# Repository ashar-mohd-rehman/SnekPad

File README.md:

I introduce you all to the SnekPad. Snekpad is a 6key macropad with an OLED display and a Volume knob. The oled display shows the stas, Volume and the SnekPad Logo. 
The volume knob is used for well, To contol volume and mute on a press. The Top keys are mapped to Copy,Paste,Cut and the bottom keys are mappable in ur desired software.
# Assembly

# PCB 

# Schematic

# Code Snippet

 # **BOM** #
| Item | Quantity | Price (USD) |
|-----|----------|-------------|
| Cherry MX Low Profile Switches | 10x | 2.70 |
| Blank DSA Keycaps | 10x | 2.20 |
| Chanzon 1N4148 Diodes | 100x | 2.73 |
| 0.91 inch OLED Display Module | 1x | 1.71 |
| Xiao RP2040 | 1x | 6.75 |
| EC11B5AI Rotary Encoder | 2x | 1.22 |
| Soldering Iron | 1x | 3.27 |
| PCB | 1x | 9.82 |
| **Total (Approx.)** |  | **31 – 35 USD** |

Link TO Bom : https://docs.google.com/spreadsheets/d/1mGxVifGTovYlbTKS4N1jqtnvdSKJnGPxNXVJJV7mGf4/edit?usp=sharing

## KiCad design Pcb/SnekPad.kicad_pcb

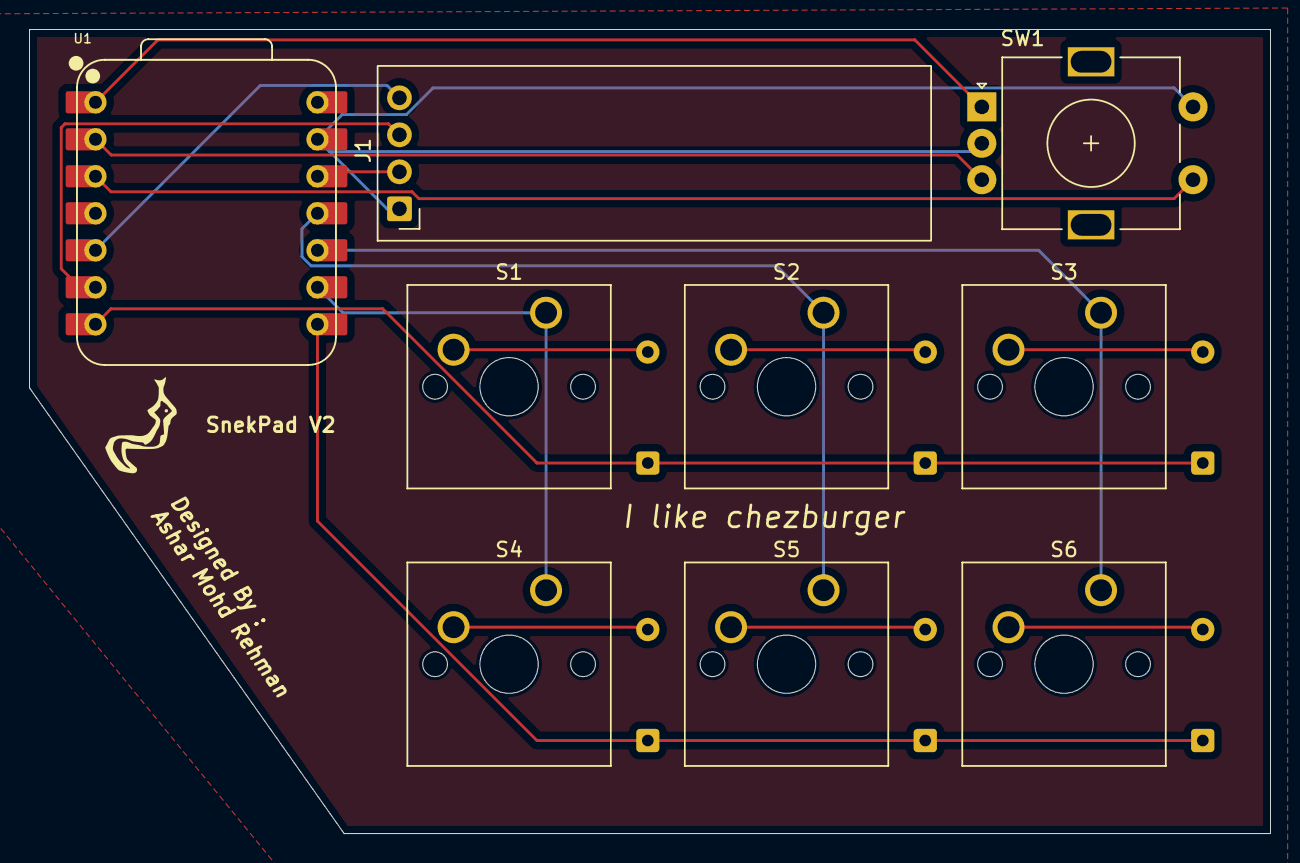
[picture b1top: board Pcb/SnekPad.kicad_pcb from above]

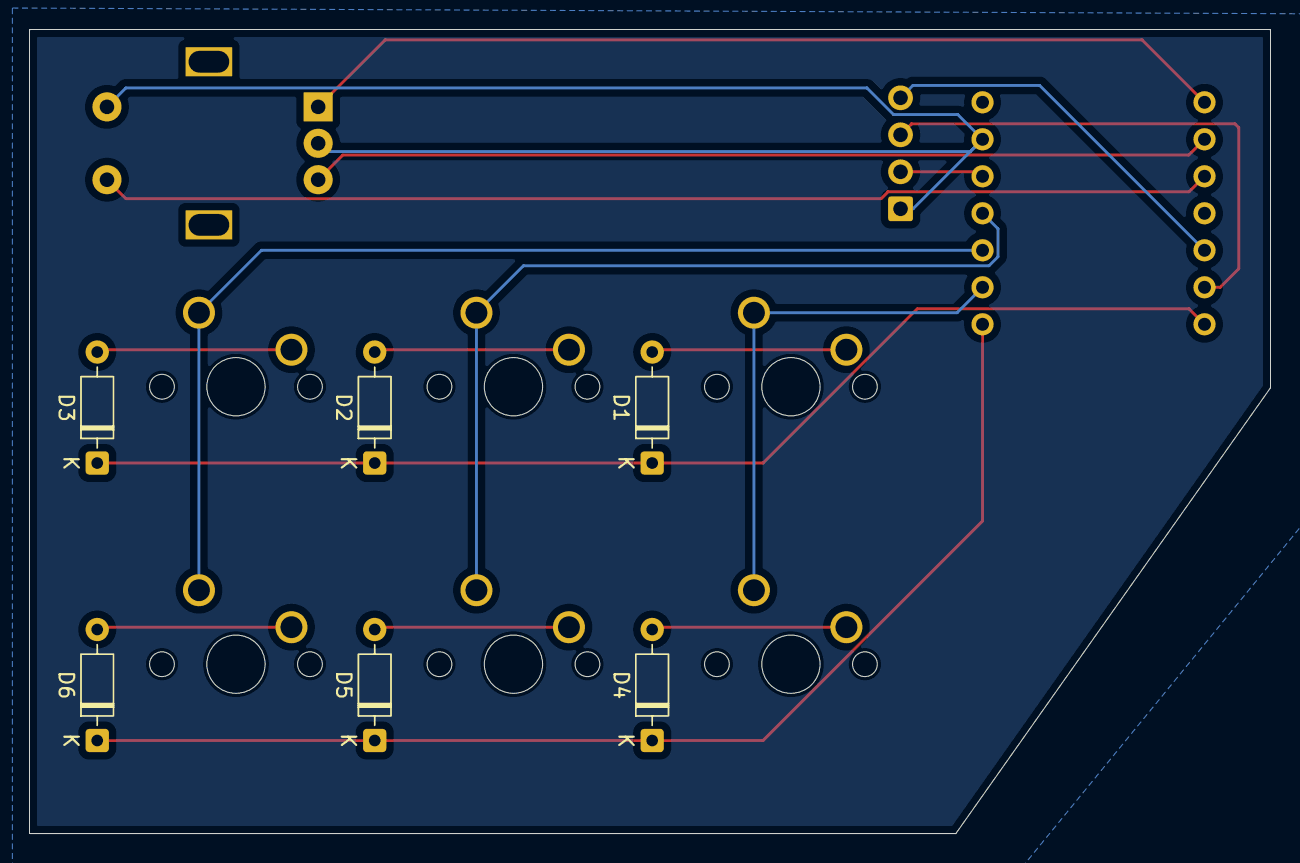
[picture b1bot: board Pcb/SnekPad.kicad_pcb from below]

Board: 2 copper layers, 85.2 x 55.2 mm, 15 parts (6 on the bottom side), 18 nets.

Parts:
D1, D2, D3, D4, D5, D6: D_DO-35_SOD27_P7.62mm_Horizontal
J1: OLED_128x32; OLED_0.91_128x32
S1, S2, S3, S4, S5, S6: SW_Cherry_MX_1.00u_PCB
SW1: RotaryEncoder_Switch; RotaryEncoder_Alps_EC11E-Switch_Vertical_H20mm
U1: XIAO-RP2040-DIP

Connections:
/Col 1: S1.1, S4.1, U1.9 (GPIO2/SCK)
/Col 2: S2.1, S5.1, U1.11 (GPIO3/MOSI)
/Col 3: S3.1, S6.1, U1.10 (GPIO4/MISO)
/Enc A: SW1.A, U1.1 (GPIO26/ADC0/A0)
/Enc B: SW1.B, U1.2 (GPIO27/ADC1/A1)
/Enc SW1: SW1.S1, U1.3 (GPIO28/ADC2/A2)
/Row 1: D1.1 (K), D2.1 (K), D3.1 (K), U1.7 (GPIO0/TX)
/Row 2: D4.1 (K), D5.1 (K), D6.1 (K), U1.8 (GPIO1/RX)
/SCL: J1.3 (SCL), U1.6 (GPIO7/SCL)
/SDA: J1.4 (SDA), U1.5 (GPIO6/SDA)
/VCC: J1.2 (VCC), U1.12 (3V3)
GND: J1.1 (GND), SW1.C, SW1.S2, U1.13 (GND)
unnamed: D1.2 (A), S1.2
unnamed: D2.2 (A), S2.2
unnamed: D3.2 (A), S3.2
unnamed: D4.2 (A), S4.2
unnamed: D5.2 (A), S5.2
unnamed: D6.2 (A), S6.2

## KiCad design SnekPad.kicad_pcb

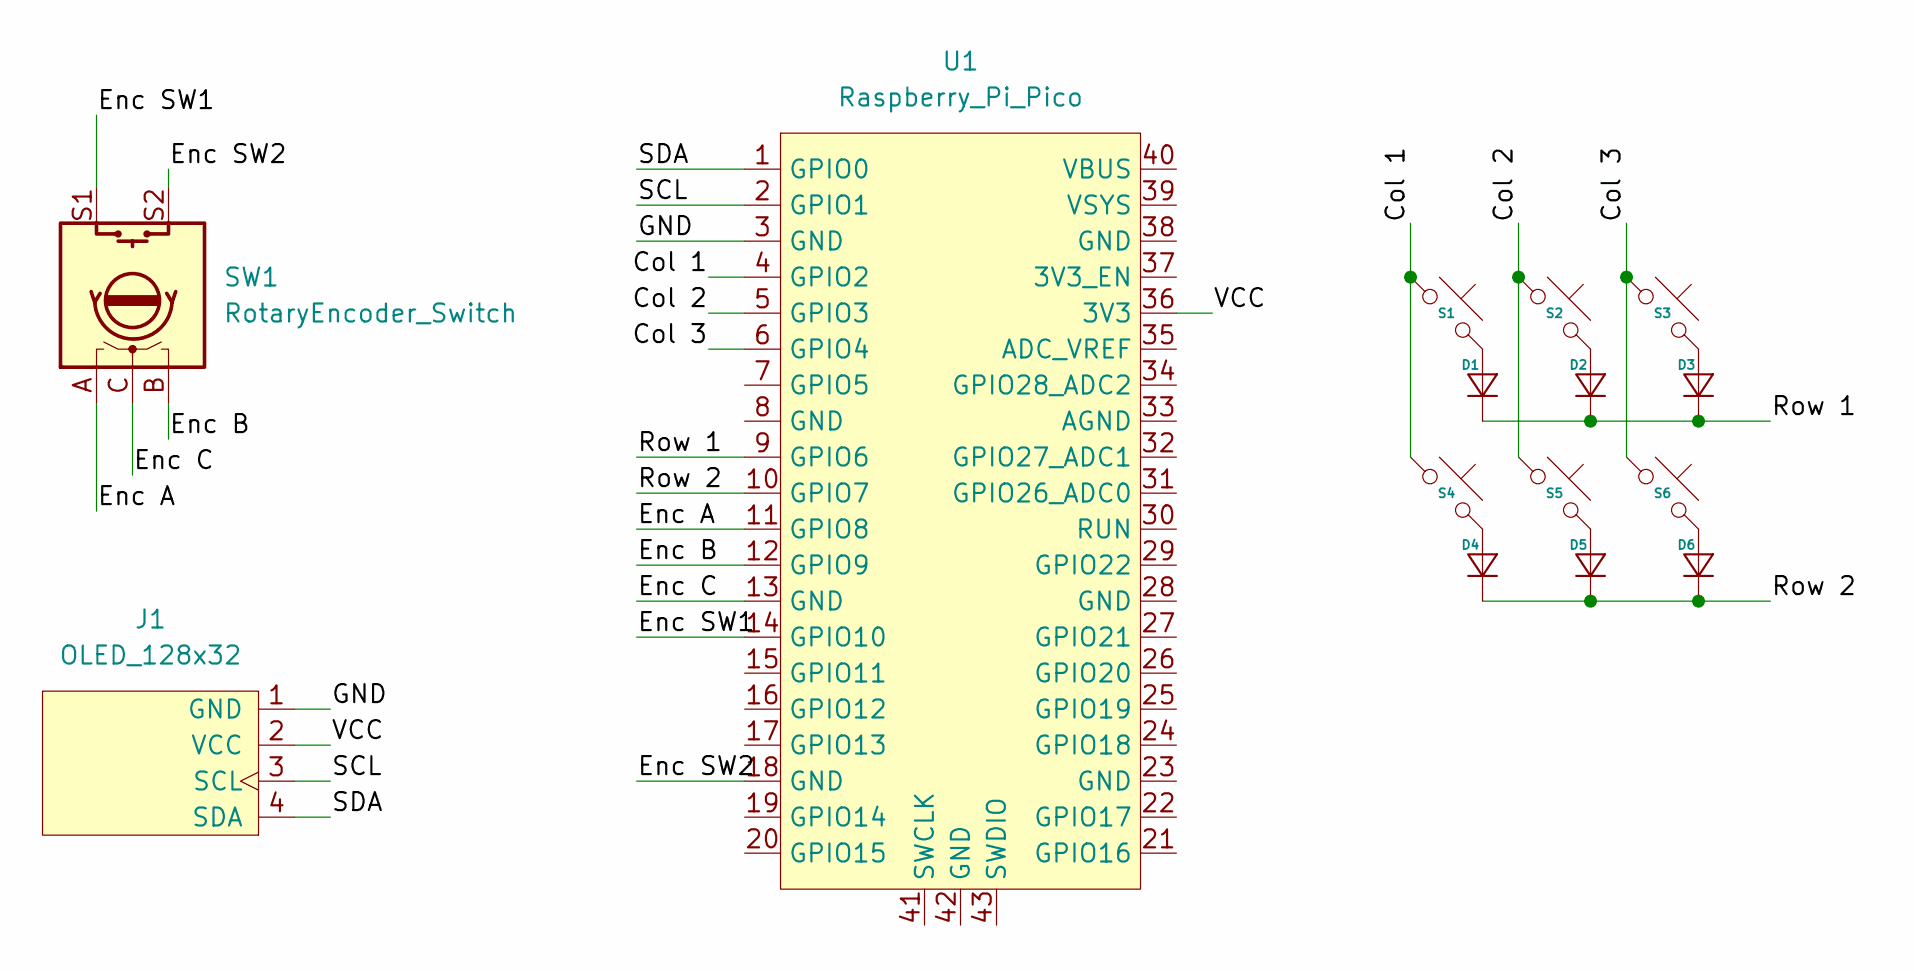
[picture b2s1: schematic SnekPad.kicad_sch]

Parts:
D1, D2, D3, D4, D5, D6: D_DO-35_SOD27_P7.62mm_Horizontal
J1: OLED_128x32
S1, S2, S3, S4, S5, S6: SW_Cherry_MX_1.00u_PCB
SW1: RotaryEncoder_Switch; RotaryEncoder_Alps_EC11E-Switch_Vertical_H20mm
U1: Raspberry_Pi_Pico; RaspberryPi_Pico_Common_THT

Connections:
/Col 1: S1.1, S4.1, U1.4 (GPIO2)
/Col 2: S2.1, S5.1, U1.5 (GPIO3)
/Col 3: S3.1, S6.1, U1.6 (GPIO4)
/Enc A: SW1.A, U1.11 (GPIO8)
/Enc B: SW1.B, U1.12 (GPIO9)
/Enc C: SW1.C, U1.13 (GND)
/Enc SW1: SW1.S1, U1.14 (GPIO10)
/Enc SW2: SW1.S2, U1.18 (GND)
/GND: J1.1 (GND), U1.3 (GND)
/Row 1: D1.1 (K), D2.1 (K), D3.1 (K), U1.9 (GPIO6)
/Row 2: D4.1 (K), D5.1 (K), D6.1 (K), U1.10 (GPIO7)
/SCL: J1.3 (SCL), U1.2 (GPIO1)
/SDA: J1.4 (SDA), U1.1 (GPIO0)
/VCC: J1.2 (VCC), U1.36 (3V3)
unnamed: D1.2 (A), S1.2
unnamed: D2.2 (A), S2.2
unnamed: D3.2 (A), S3.2
unnamed: D4.2 (A), S4.2
unnamed: D5.2 (A), S5.2
unnamed: D6.2 (A), S6.2

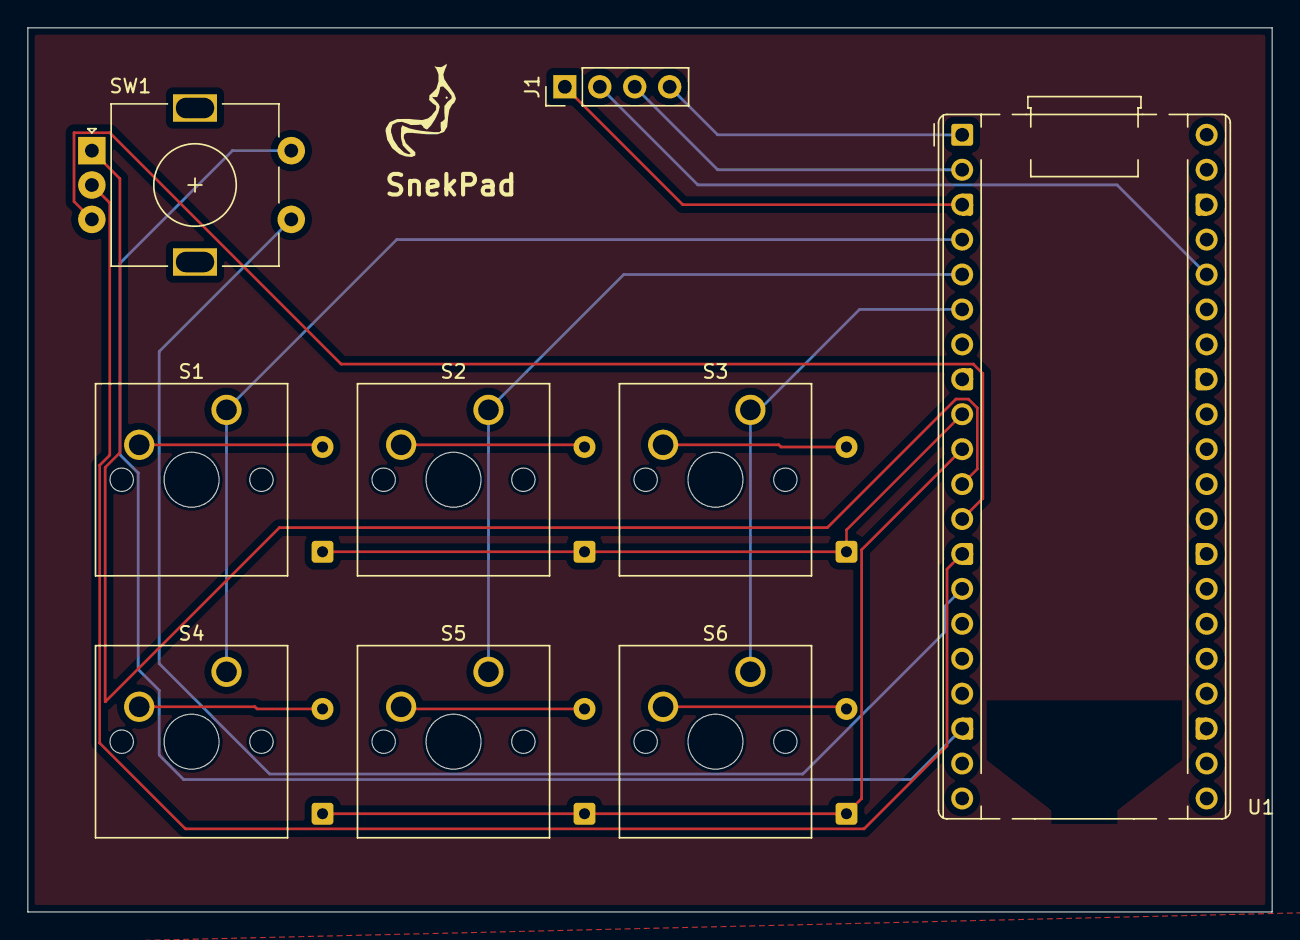
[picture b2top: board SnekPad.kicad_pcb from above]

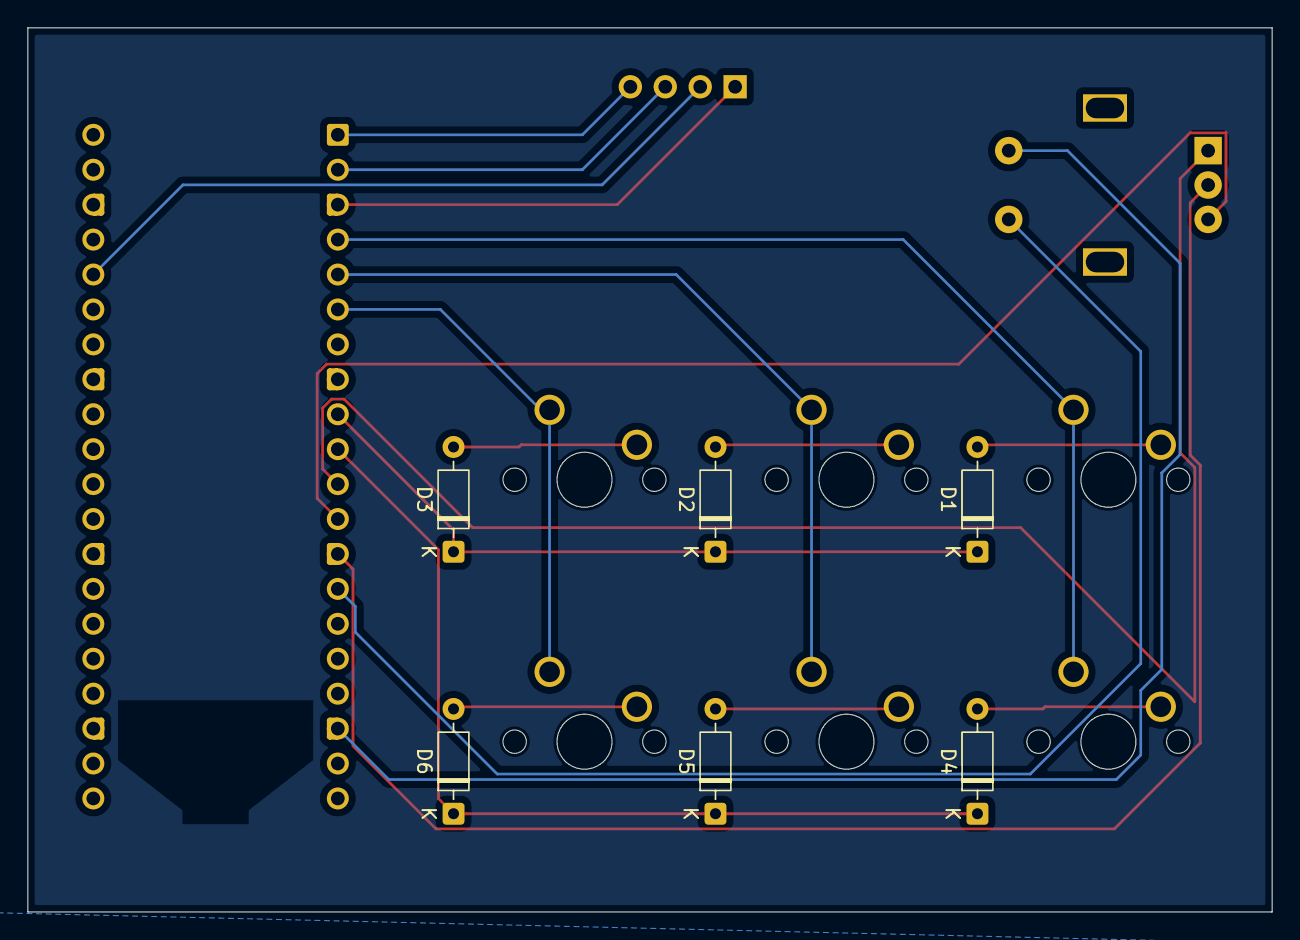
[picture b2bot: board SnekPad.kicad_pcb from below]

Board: 2 copper layers, 90.5 x 64.3 mm, 16 parts (6 on the bottom side), 20 nets.

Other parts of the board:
SnekPad: LOGO; snek

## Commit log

2026-01-24 Rename SnekPad.kicad_pcb to Pcb/SnekPad.kicad_pcb
2026-01-24 Rename SnekPad.kicad_prl to Pcb/SnekPad.kicad_prl
2026-01-24 Rename SnekPad.kicad_pro to Pcb/SnekPad.kicad_pro
2026-01-24 Rename SnekPad.kicad_sch to Pcb/SnekPad.kicad_sch
2026-01-24 Rename main.py to Firmware KMK/main.py
2026-01-27 Create Bom Csv
2026-01-27 Create Link to BOM
2026-01-27 Update Link to BOM
2026-01-27 Remove BOM
2026-01-27 Create Link
2026-02-02 Create Gerber
